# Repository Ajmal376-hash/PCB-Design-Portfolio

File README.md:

# PCB-Design-Portfolio
PCB designs developed using Autodesk EAGLECAD for electronics and embedded systems applications.

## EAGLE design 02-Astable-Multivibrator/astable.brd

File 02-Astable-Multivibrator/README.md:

# Astable Multivibrator PCB

A compact **Astable Multivibrator** circuit designed in **Autodesk EAGLE** using BC547 transistors to generate continuous oscillation and alternate LED blinking.

### Features

* BC547 transistor-based design
* Two alternating LED outputs
* Double-layer PCB
* Polygon copper pour
* Compact PCB layout
* Schematic and PCB design included

### Tools

* Autodesk EAGLE

### Author

**Muhammad Ajmal**

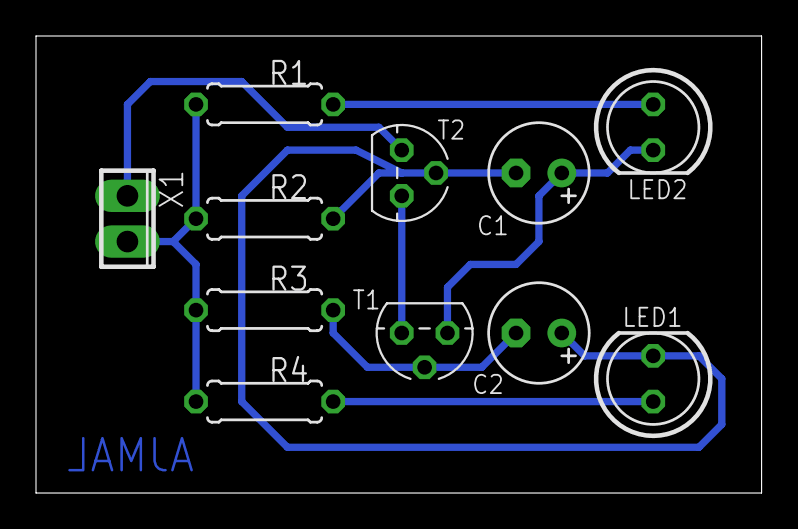
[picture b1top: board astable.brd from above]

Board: 2 copper layers, 40.3 x 25.4 mm, 11 parts (0 on the bottom side), 8 nets.

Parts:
C1, C2: 10uF; E2,5-6
LED1, LED2: LED5MM
R1, R4: 100E; 0207/7
R2, R3: 100K; 0207/7
T1, T2: BC547; TO92
X1: 2POL254

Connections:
unnamed: R1.2, R2.2, R3.2, R4.2, X1.2
unnamed: LED1.A, R4.1
unnamed: LED2.A, R1.1
unnamed: C1.+, LED2.K, T1.3
unnamed: C1.-, C2.+, LED1.K, R2.1, T2.2
unnamed: C2.-, R3.1, T1.2
unnamed: T1.1, T2.1
S$1: T2.3, X1.1

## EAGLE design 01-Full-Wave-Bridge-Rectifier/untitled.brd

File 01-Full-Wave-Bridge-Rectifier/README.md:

# Full-Wave Bridge Rectifier – 9V Power Supply

A compact **double-layer PCB** designed using **Autodesk EAGLE** for AC-to-DC conversion and regulated 9V output.

### Features

* Full-wave bridge rectifier using M7 diodes
* 470 µF filtering capacitor
* LM7809 voltage regulator
* Green power indicator LED
* 470 Ω current-limiting resistor
* **Double-layer PCB with polygon copper pour**

### Tools

* Autodesk EAGLE
* Schematic & PCB Layout Design

### Author

**Muhammad Ajmal**

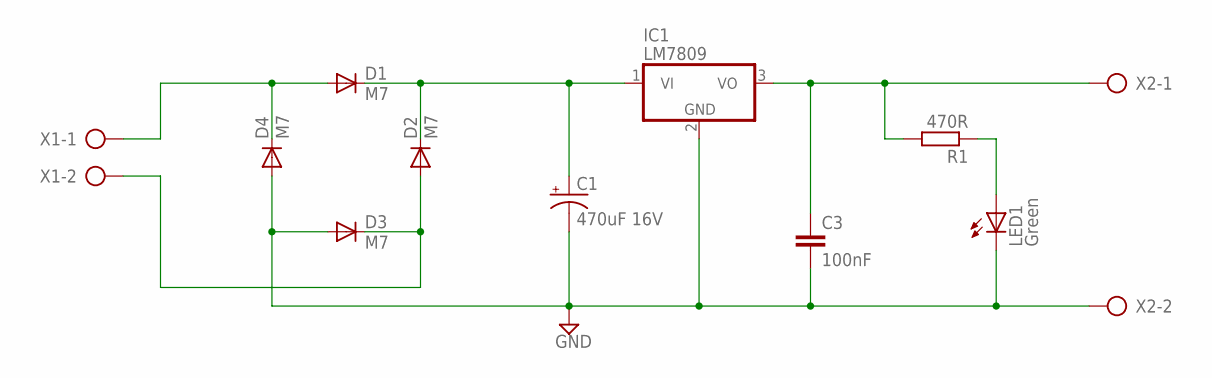
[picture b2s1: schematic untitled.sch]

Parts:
C1: 470uF 16V; E2,5-6
C3: 100nF; C0805
D1, D2, D3, D4: M7; SOD-123_MINI-SMA
IC1: LM7809; TO220H
LED1: Green; LED5MM
R1: 470R; M3516
X1, X2: AK500/2

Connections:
GND: C1.-, C3.2, D3.A, D4.A, IC1.2 (GND), LED1.K (C), X2.2
unnamed: C1.+, D1.C, D2.C, IC1.1 (VI)
unnamed: D2.A, D3.C, X1.2
unnamed: D1.A, D4.C, X1.1
unnamed: C3.1, IC1.3 (VO), R1.2, X2.1
unnamed: LED1.A, R1.1

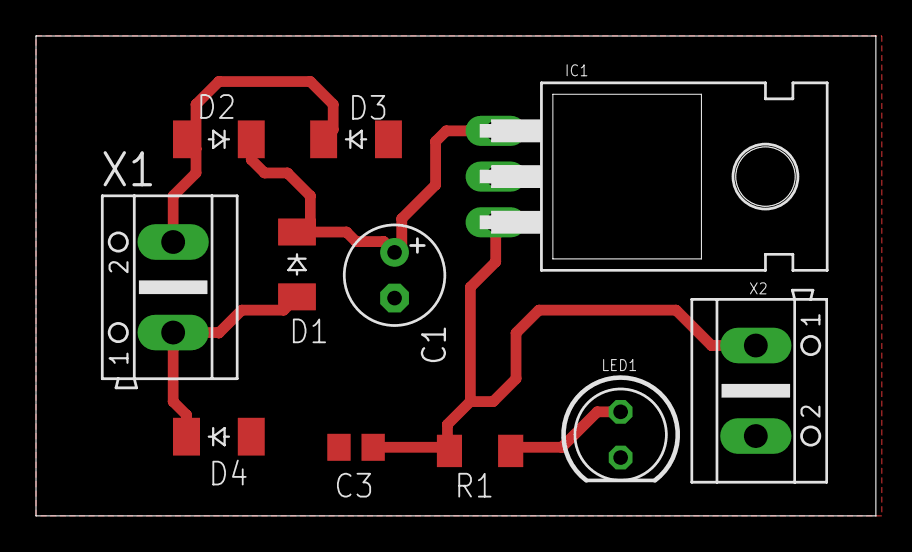
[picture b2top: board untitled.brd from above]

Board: 2 copper layers, 46.7 x 26.7 mm, 11 parts (0 on the bottom side), 6 nets.
